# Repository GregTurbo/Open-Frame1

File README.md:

# Pummel Prism Pico (WIP)

An open-source All Button fight stick for traditional fighters, prioritizing small size and 3d printablitiy.

[FeralAI's code (gp2040)](https://github.com/FeralAI/GP2040)

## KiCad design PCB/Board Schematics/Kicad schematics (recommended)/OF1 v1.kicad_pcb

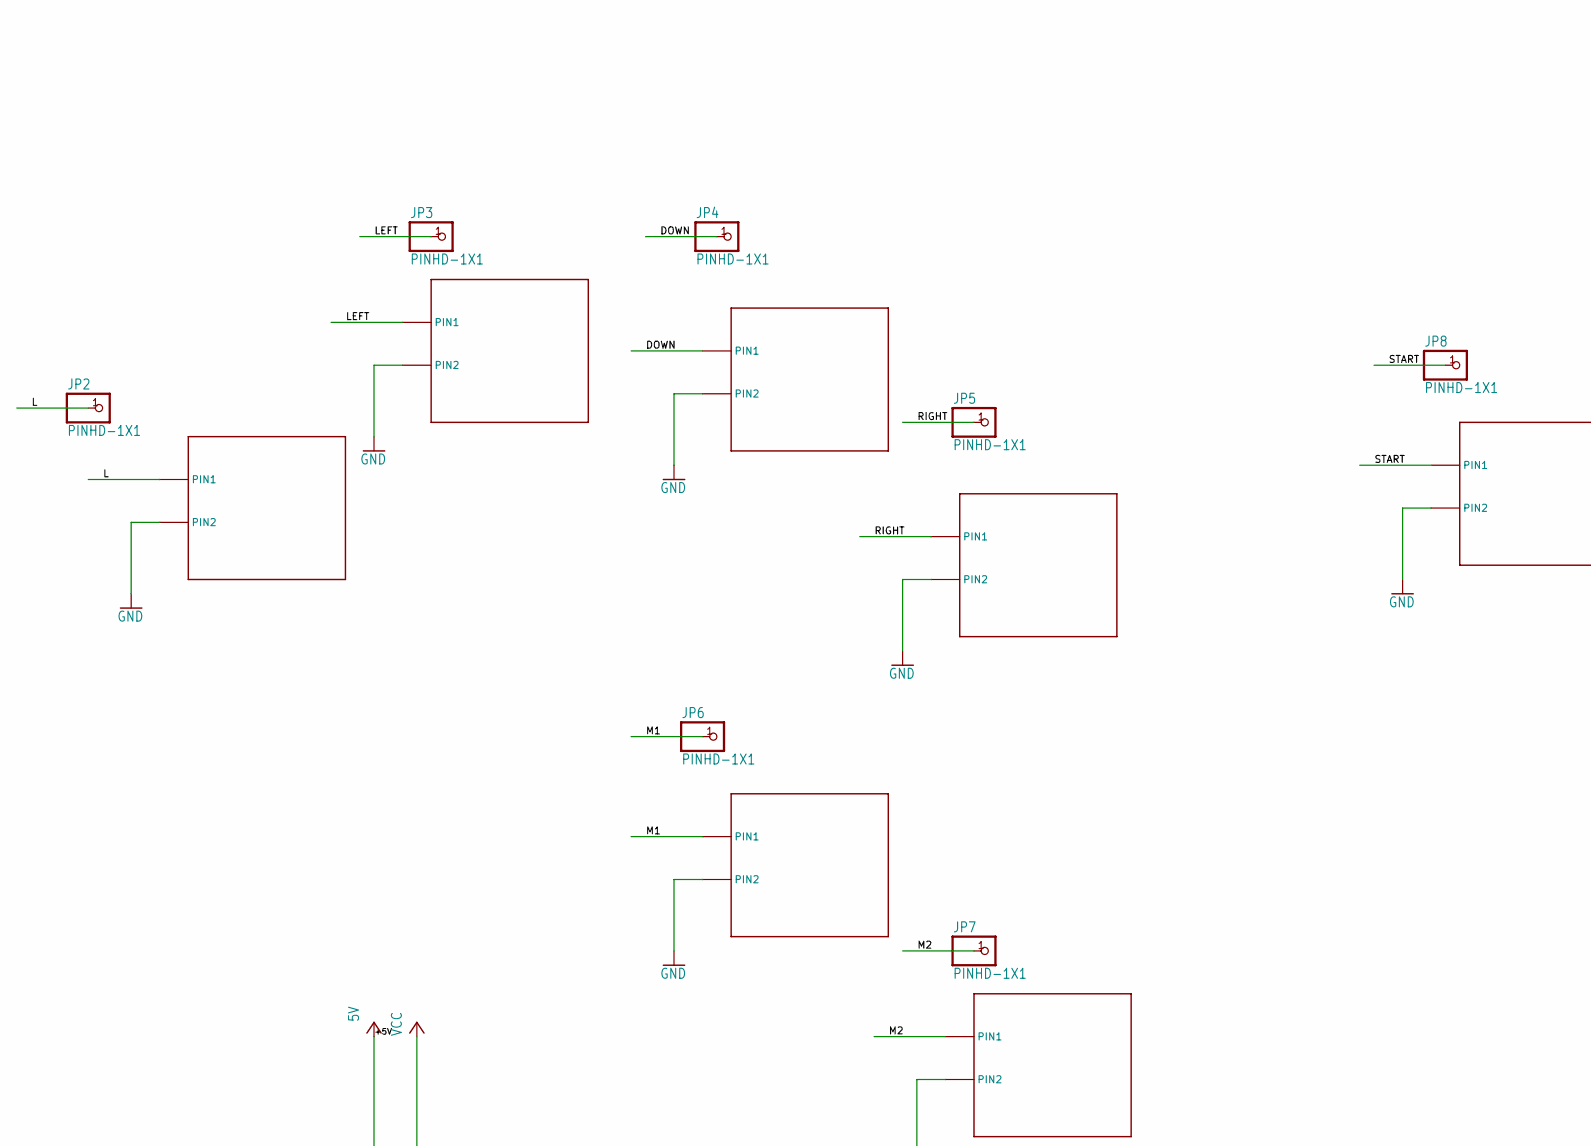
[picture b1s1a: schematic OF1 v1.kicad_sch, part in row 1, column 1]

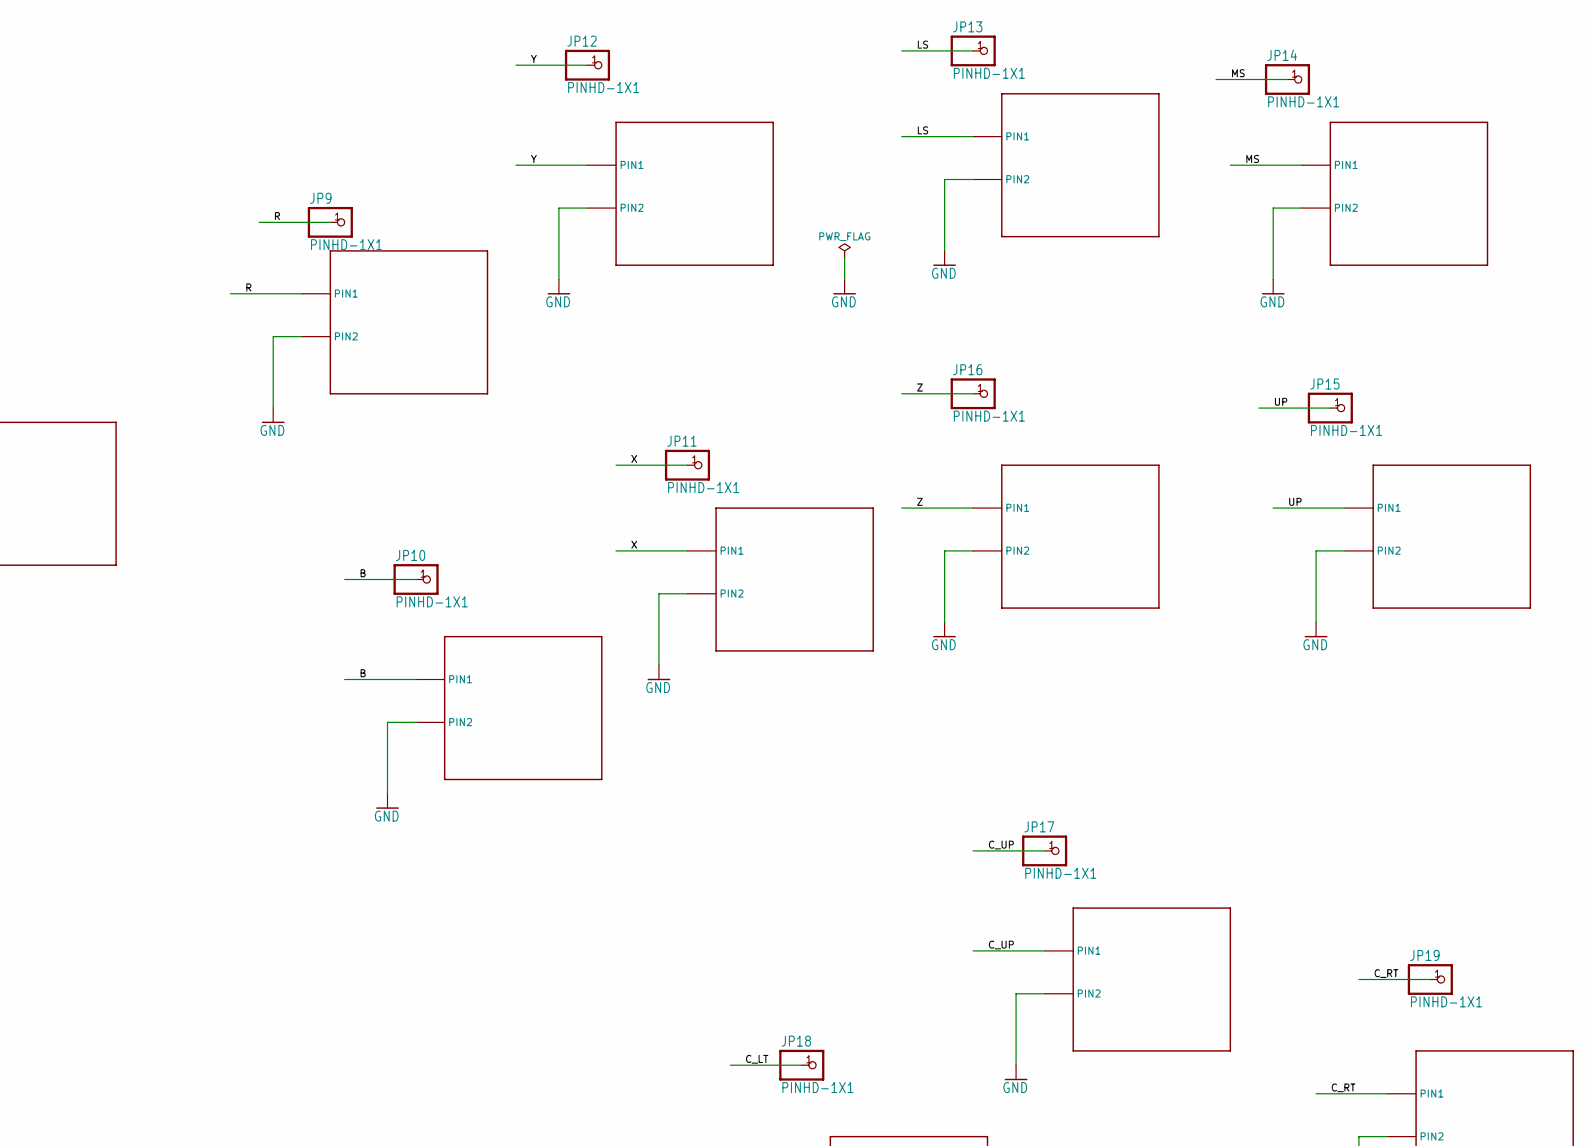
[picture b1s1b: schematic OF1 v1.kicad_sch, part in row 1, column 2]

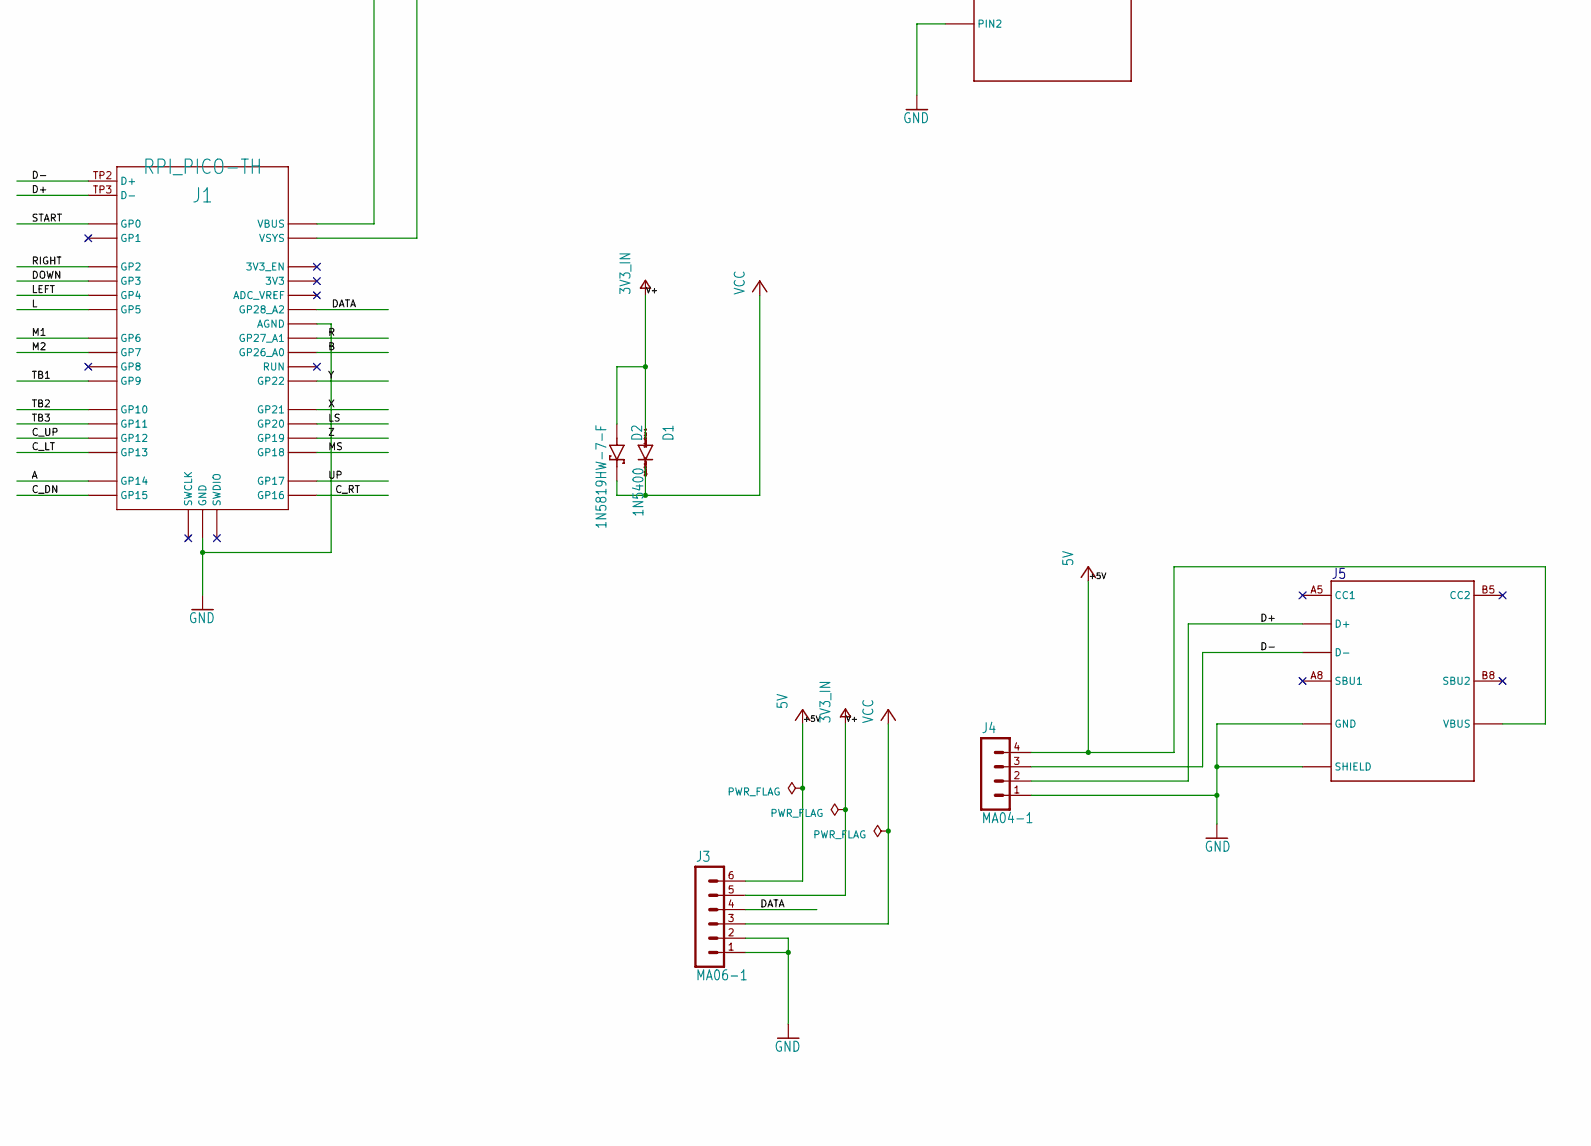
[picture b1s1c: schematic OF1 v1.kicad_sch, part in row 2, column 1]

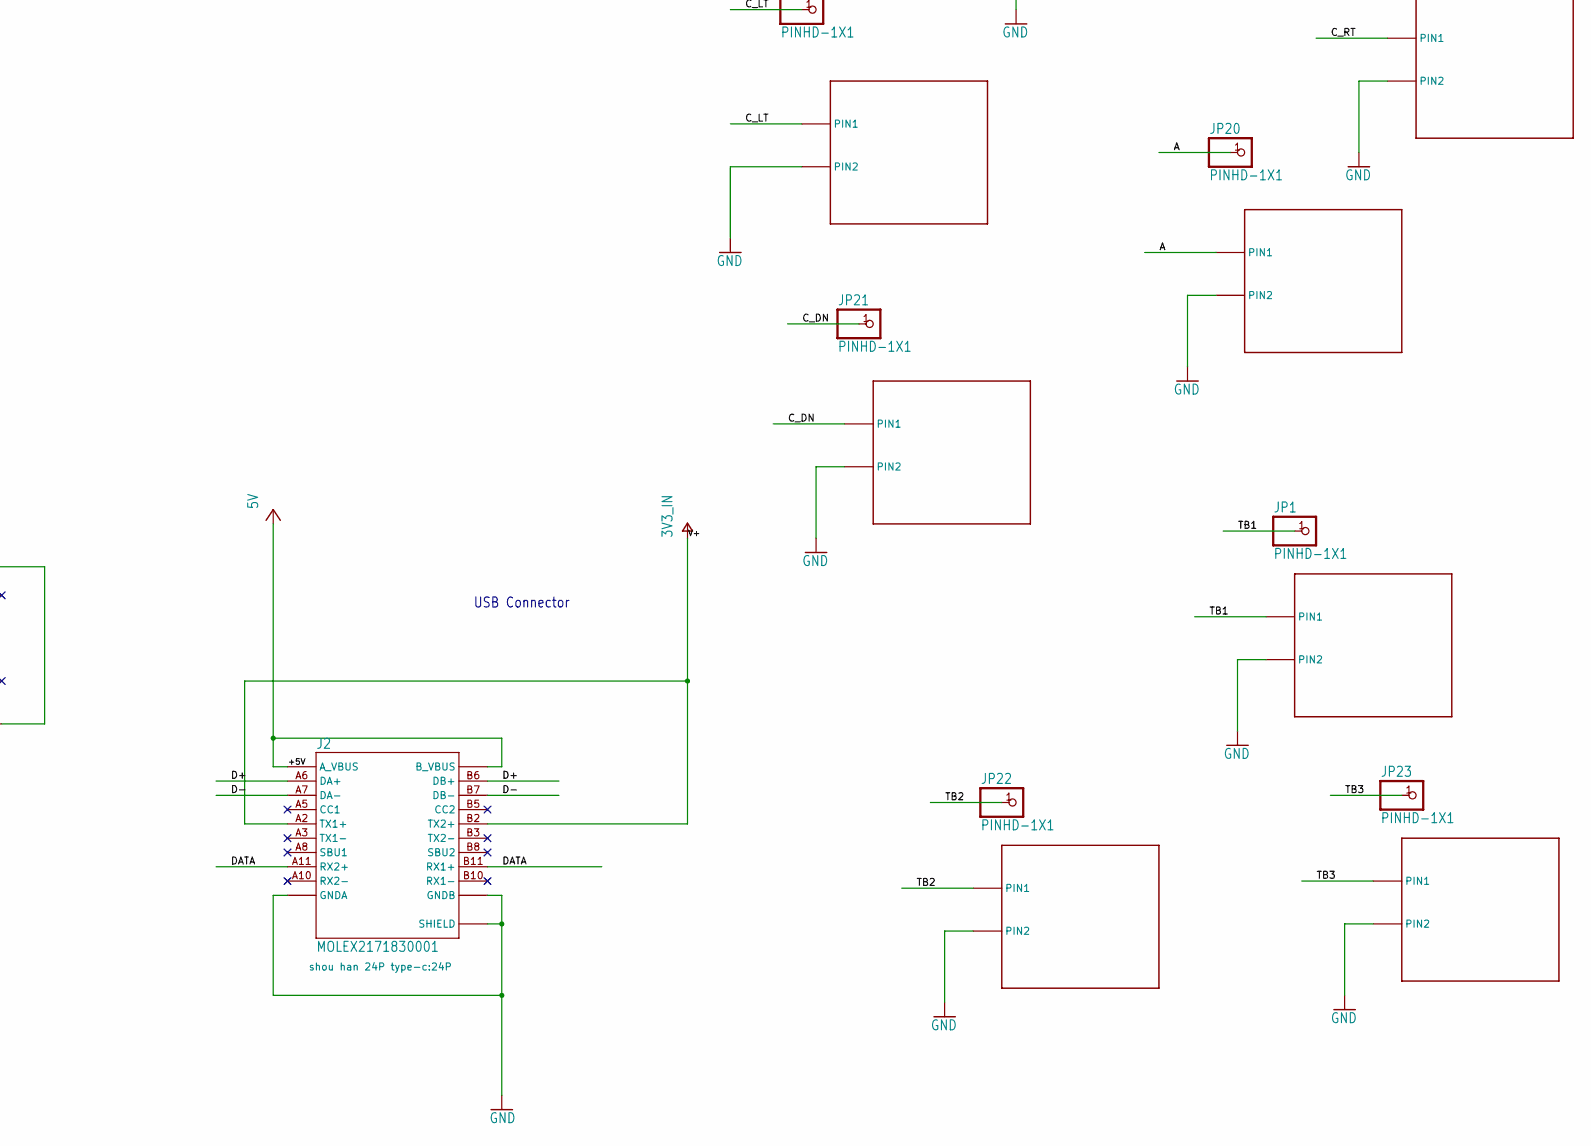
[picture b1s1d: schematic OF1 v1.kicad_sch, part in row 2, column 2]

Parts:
D1: 1N5400; DO201-15
D2: 1N5819HW-7-F; SOD3715X145N
J1: RPI_PICO-TH; RPI_PICO_TH
J2: MOLEX2171830001; 24P
J3: MA06-1
J4: MA04-1
J5: GT-USB-7010; 16P
JP1, JP2, JP3, JP4, JP5, JP6, JP7, JP8, JP9, JP10, JP11, JP12, JP13, JP14, JP15, JP16, JP17, JP18, JP19, JP20, JP21, JP22, JP23: PINHD-1X1; 1X01
U$1, U$2, U$3, U$4, U$5, U$6, U$7, U$8, U$9, U$10, U$11, U$12, U$13, U$14, U$15, U$16, U$17, U$18, U$19, U$20, U$21, U$22, U$23: MX-B; MX-BOTH

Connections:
+5V: J1.VBUS, J2.A4 (A_VBUS), J2.A9 (A_VBUS), J2.B4 (B_VBUS), J2.B9 (B_VBUS), J3.6, J4.4, J5.A4/B9 (VBUS), J5.B4/A9 (VBUS)
/A: J1.GP14, JP20.1, U$20.P$2 (PIN1), U$20.P$3 (PIN1)
/B: J1.GP26_A0, JP10.1, U$13.P$2 (PIN1), U$13.P$3 (PIN1)
/C_DN: J1.GP15, JP21.1, U$21.P$2 (PIN1), U$21.P$3 (PIN1)
/C_LT: J1.GP13, JP18.1, U$18.P$2 (PIN1), U$18.P$3 (PIN1)
/C_RT: J1.GP16, JP19.1, U$19.P$2 (PIN1), U$19.P$3 (PIN1)
/C_UP: J1.GP12, JP17.1, U$17.P$2 (PIN1), U$17.P$3 (PIN1)
/D+: J1.TP3 (D-), J2.A6 (DA+), J2.B6 (DB+), J4.2, J5.A6 (D+), J5.B6 (D+)
/D-: J1.TP2 (D+), J2.A7 (DA-), J2.B7 (DB-), J4.3, J5.A7 (D-), J5.B7 (D-)
/DATA: J1.GP28_A2, J2.A11 (RX2+), J2.B11 (RX1+), J3.4
/DOWN: J1.GP3, JP4.1, U$4.P$2 (PIN1), U$4.P$3 (PIN1)
/L: J1.GP5, JP2.1, U$1.P$2 (PIN1), U$1.P$3 (PIN1)
/LEFT: J1.GP4, JP3.1, U$2.P$2 (PIN1), U$2.P$3 (PIN1)
/LS: J1.GP20, JP13.1, U$11.P$2 (PIN1), U$11.P$3 (PIN1)
/M1: J1.GP6, JP6.1, U$6.P$2 (PIN1), U$6.P$3 (PIN1)
/M2: J1.GP7, JP7.1, U$7.P$2 (PIN1), U$7.P$3 (PIN1)
/MS: J1.GP18, JP14.1, U$12.P$2 (PIN1), U$12.P$3 (PIN1)
/R: J1.GP27_A1, JP9.1, U$9.P$2 (PIN1), U$9.P$3 (PIN1)
/RIGHT: J1.GP2, JP5.1, U$5.P$2 (PIN1), U$5.P$3 (PIN1)
/START: J1.GP0, JP8.1, U$8.P$2 (PIN1), U$8.P$3 (PIN1)
/TB1: J1.GP9, JP1.1, U$3.P$2 (PIN1), U$3.P$3 (PIN1)
/TB2: J1.GP10, JP22.1, U$22.P$2 (PIN1), U$22.P$3 (PIN1)
/TB3: J1.GP11, JP23.1, U$23.P$2 (PIN1), U$23.P$3 (PIN1)
/UP: J1.GP17, JP15.1, U$16.P$2 (PIN1), U$16.P$3 (PIN1)
/X: J1.GP21, JP11.1, U$14.P$2 (PIN1), U$14.P$3 (PIN1)
/Y: J1.GP22, JP12.1, U$10.P$2 (PIN1), U$10.P$3 (PIN1)
/Z: J1.GP19, JP16.1, U$15.P$2 (PIN1), U$15.P$3 (PIN1)
GND: J1.AGND, J1.GND@1 (GND), J1.GND@2 (GND), J1.GND@3 (GND), J1.GND@4 (GND), J1.GND@5 (GND), J1.GND@6 (GND), J1.GND@7 (GND), J1.GND@8 (GND), J2.A1 (GNDA), J2.A12 (GNDA), J2.B1 (GNDB), J2.B12 (GNDB), J2.SHIELD1 (SHIELD), J2.SHIELD2 (SHIELD), J2.SHIELD3 (SHIELD), J2.SHIELD4 (SHIELD), J3.1, J3.2, J4.1, J5.A1/B12 (GND), J5.B1/A12 (GND), J5.SHIELD1 (SHIELD), J5.SHIELD2 (SHIELD), J5.SHIELD3 (SHIELD), J5.SHIELD4 (SHIELD), U$1.P$1 (PIN2), U$1.P$4 (PIN2), U$2.P$1 (PIN2), U$2.P$4 (PIN2), U$3.P$1 (PIN2), U$3.P$4 (PIN2), U$4.P$1 (PIN2), U$4.P$4 (PIN2), U$5.P$1 (PIN2), U$5.P$4 (PIN2), U$6.P$1 (PIN2), U$6.P$4 (PIN2), U$7.P$1 (PIN2), U$7.P$4 (PIN2), U$8.P$1 (PIN2), U$8.P$4 (PIN2), U$9.P$1 (PIN2), U$9.P$4 (PIN2), U$10.P$1 (PIN2), U$10.P$4 (PIN2), U$11.P$1 (PIN2), U$11.P$4 (PIN2), U$12.P$1 (PIN2), U$12.P$4 (PIN2), U$13.P$1 (PIN2), U$13.P$4 (PIN2), U$14.P$1 (PIN2), U$14.P$4 (PIN2), U$15.P$1 (PIN2), U$15.P$4 (PIN2), U$16.P$1 (PIN2), U$16.P$4 (PIN2), U$17.P$1 (PIN2), U$17.P$4 (PIN2), U$18.P$1 (PIN2), U$18.P$4 (PIN2), U$19.P$1 (PIN2), U$19.P$4 (PIN2), U$20.P$1 (PIN2), U$20.P$4 (PIN2), U$21.P$1 (PIN2), U$21.P$4 (PIN2), U$22.P$1 (PIN2), U$22.P$4 (PIN2), U$23.P$1 (PIN2), U$23.P$4 (PIN2)
V+: D1.A, D2.A, J2.A2 (TX1+), J2.B2 (TX2+), J3.5
VCC: D1.C, D2.C (K), J1.VSYS, J3.3

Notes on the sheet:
USB Connector

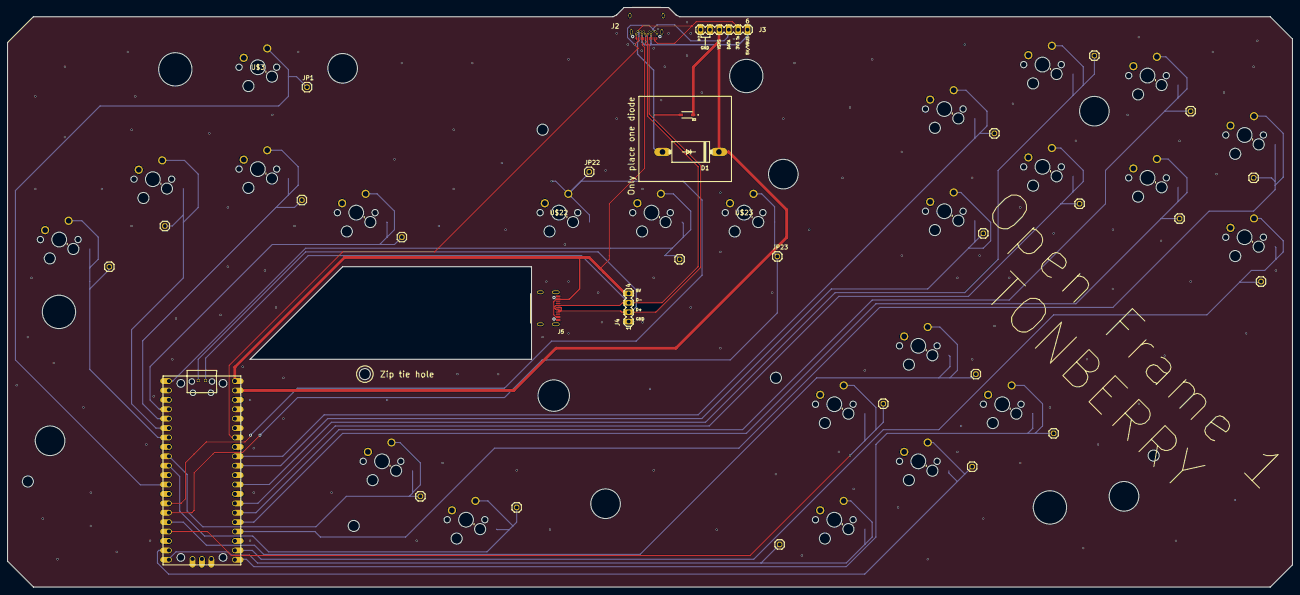
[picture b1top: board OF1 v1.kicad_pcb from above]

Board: 2 copper layers, 347.0 x 156.5 mm, 70 parts (0 on the bottom side), 30 nets.

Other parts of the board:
@HOLE0, @HOLE1, @HOLE2, @HOLE3, @HOLE4, @HOLE5, @HOLE6, @HOLE7, @HOLE8, @HOLE9, @HOLE10, @HOLE11, @HOLE12, @HOLE13, @HOLE14, @HOLE15, @HOLE16: (no value)

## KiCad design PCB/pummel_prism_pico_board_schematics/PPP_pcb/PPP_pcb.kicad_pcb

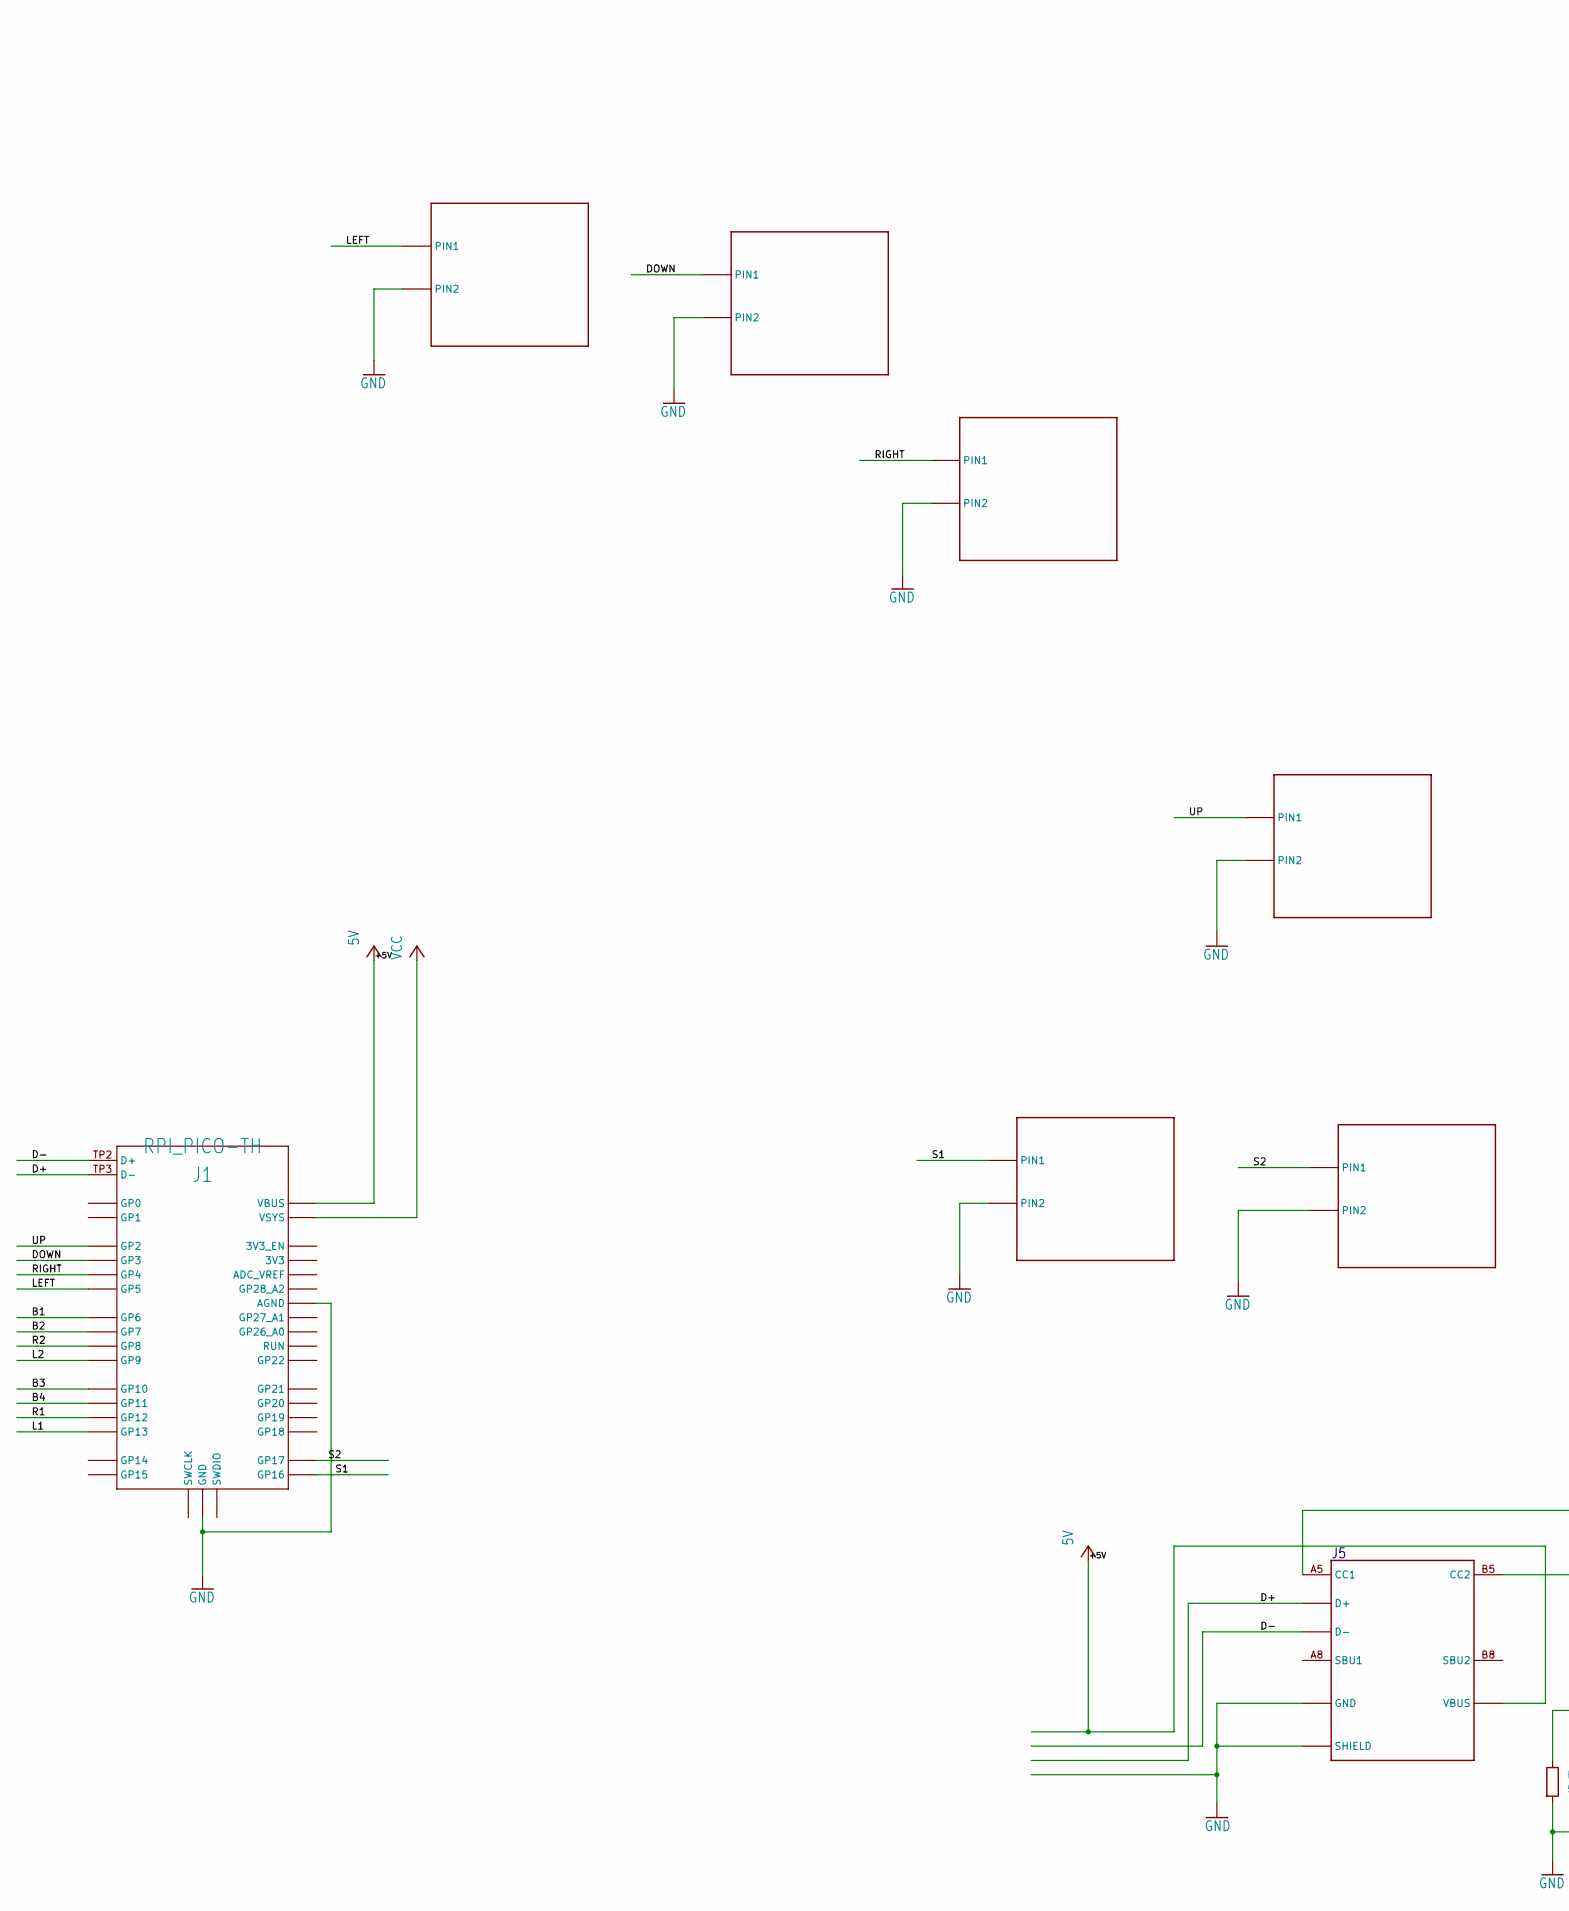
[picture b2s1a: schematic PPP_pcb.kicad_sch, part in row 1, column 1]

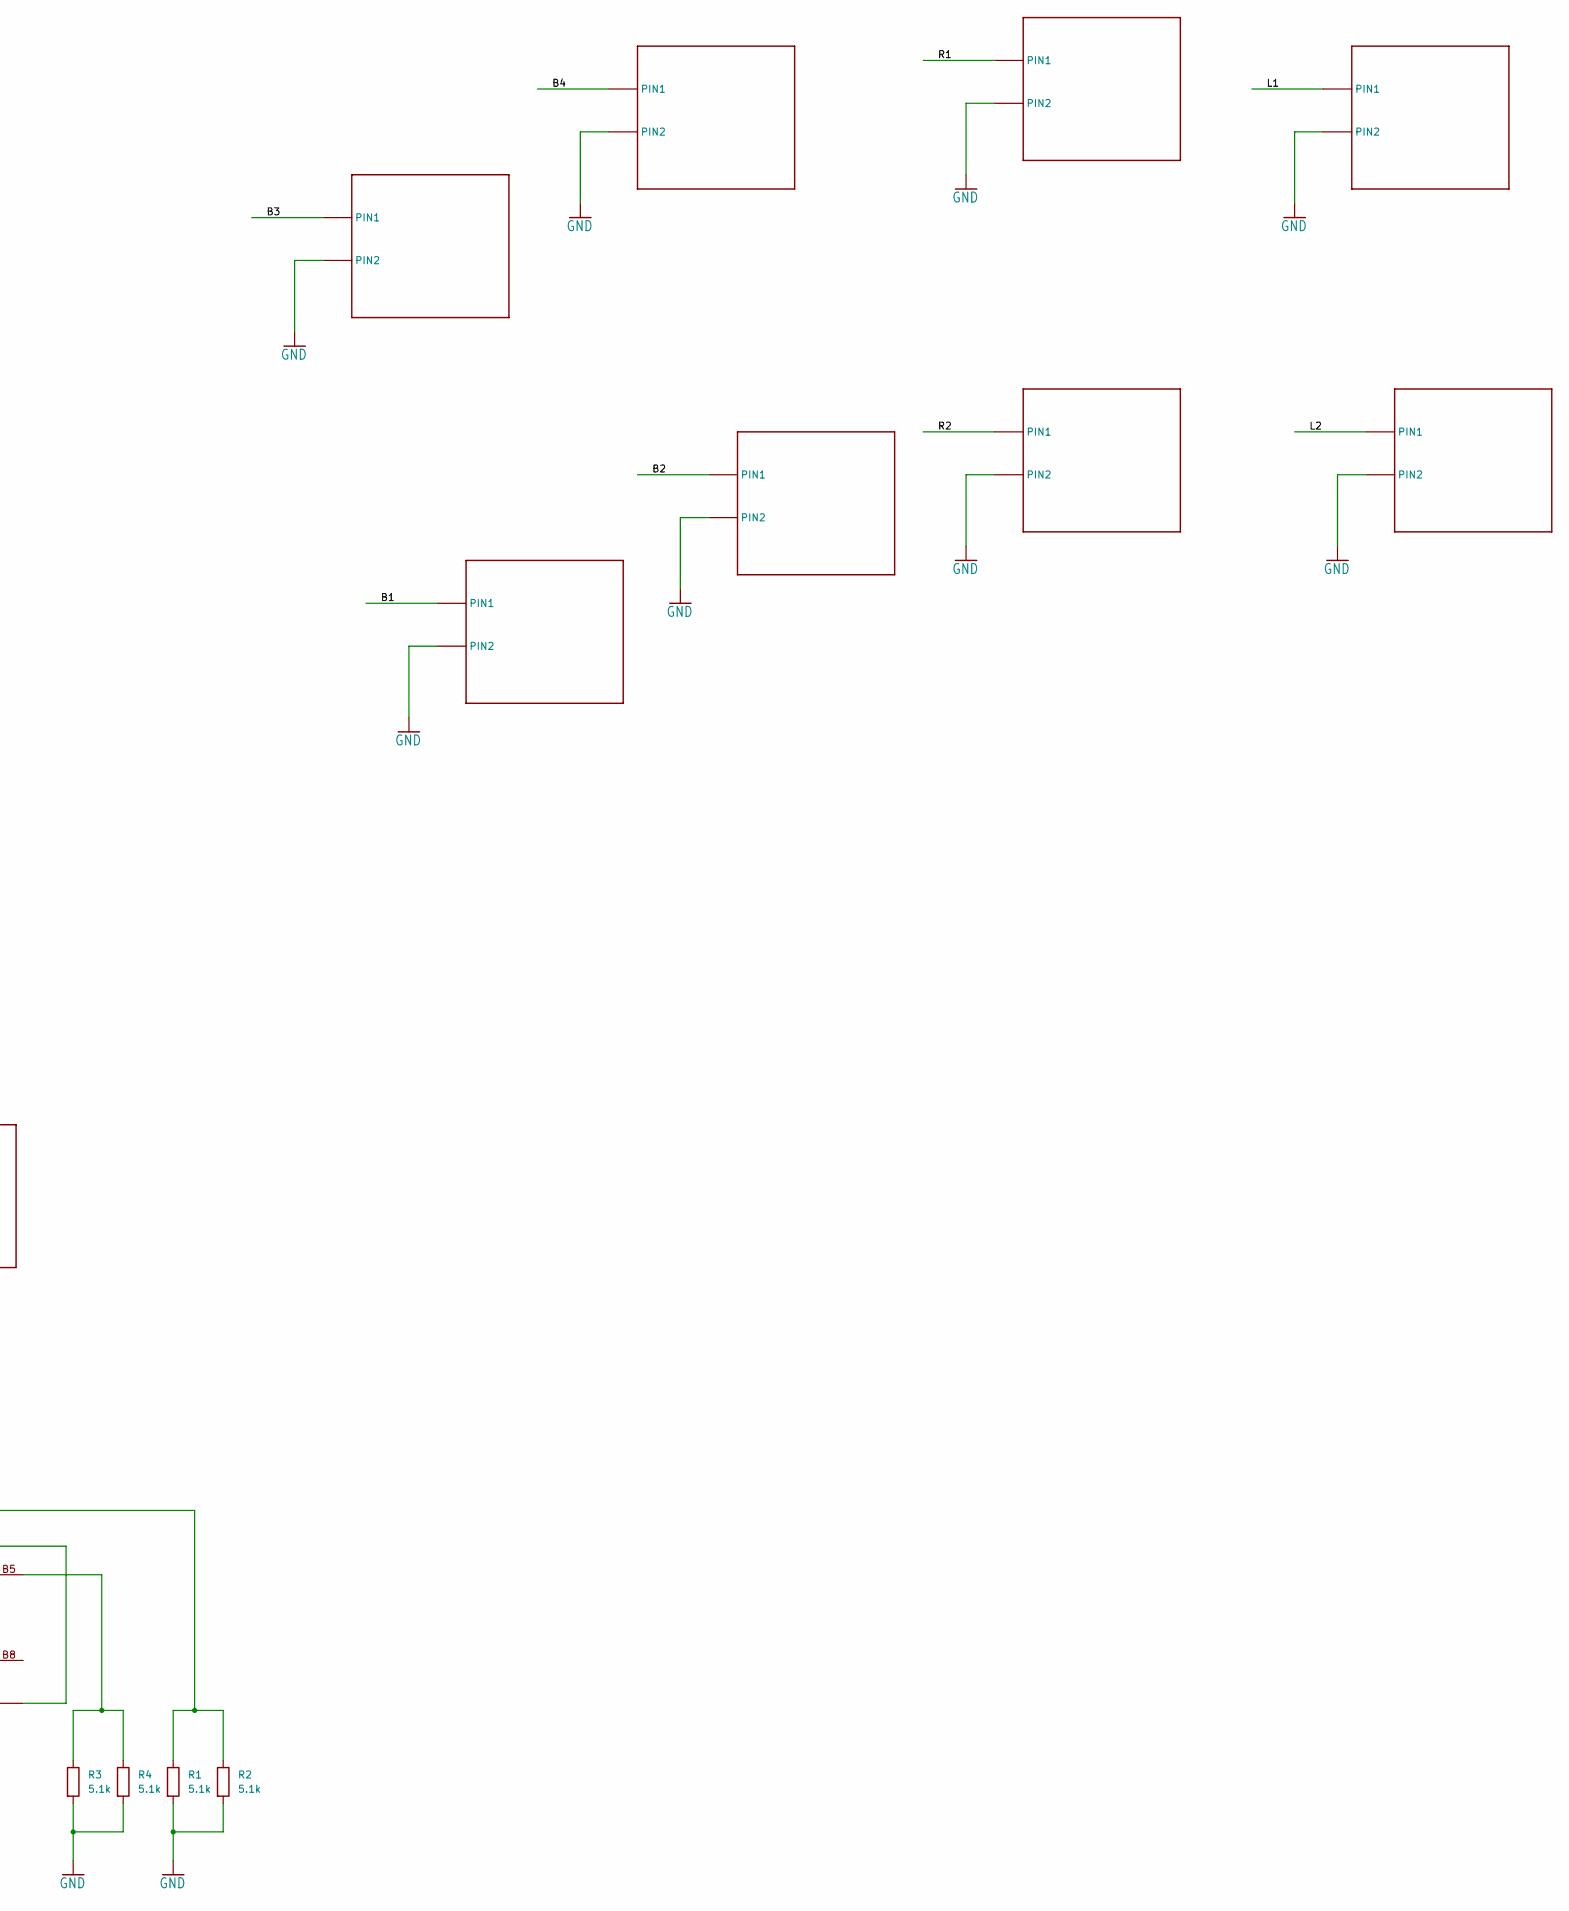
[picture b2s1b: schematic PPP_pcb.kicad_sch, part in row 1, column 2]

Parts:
J1: RPI_PICO-TH; RPI_PICO_TH
J5: GT-USB-7010; 16P
R1, R3: 5.1k; R_Axial_DIN0207_L6.3mm_D2.5mm_P7.62mm_Horizontal
R2, R4: 5.1k; R_0603_1608Metric
U$2, U$4, U$5, U$6, U$8, U$9, U$10, U$11, U$12, U$13, U$14, U$15, U$16, U$18: MX-B; MX-BOTH

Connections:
+5V: J1.VBUS, J5.A4/B9 (VBUS), J5.B4/A9 (VBUS)
/B1: J1.GP6, U$13.P$2 (PIN1), U$13.P$3 (PIN1)
/B2: J1.GP7, U$14.P$2 (PIN1), U$14.P$3 (PIN1)
/B3: J1.GP10, U$9.P$2 (PIN1), U$9.P$3 (PIN1)
/B4: J1.GP11, U$10.P$2 (PIN1), U$10.P$3 (PIN1)
/D+: J1.TP3 (D-), J5.A6 (D+), J5.B6 (D+)
/D-: J1.TP2 (D+), J5.A7 (D-), J5.B7 (D-)
/DOWN: J1.GP3, U$4.P$2 (PIN1), U$4.P$3 (PIN1)
/L1: J1.GP13, U$12.P$2 (PIN1), U$12.P$3 (PIN1)
/L2: J1.GP9, U$16.P$2 (PIN1), U$16.P$3 (PIN1)
/LEFT: J1.GP5, U$2.P$2 (PIN1), U$2.P$3 (PIN1)
/R1: J1.GP12, U$11.P$2 (PIN1), U$11.P$3 (PIN1)
/R2: J1.GP8, U$15.P$2 (PIN1), U$15.P$3 (PIN1)
/RIGHT: J1.GP4, U$5.P$2 (PIN1), U$5.P$3 (PIN1)
/S1: J1.GP16, U$8.P$2 (PIN1), U$8.P$3 (PIN1)
/S2: J1.GP17, U$18.P$2 (PIN1), U$18.P$3 (PIN1)
/UP: J1.GP2, U$6.P$2 (PIN1), U$6.P$3 (PIN1)
GND: J1.AGND, J1.GND@1 (GND), J1.GND@2 (GND), J1.GND@3 (GND), J1.GND@4 (GND), J1.GND@5 (GND), J1.GND@6 (GND), J1.GND@7 (GND), J1.GND@8 (GND), J5.A1/B12 (GND), J5.B1/A12 (GND), J5.SHIELD1 (SHIELD), J5.SHIELD2 (SHIELD), J5.SHIELD3 (SHIELD), J5.SHIELD4 (SHIELD), R1.2, R2.2, R3.2, R4.2, U$2.P$1 (PIN2), U$2.P$4 (PIN2), U$4.P$1 (PIN2), U$4.P$4 (PIN2), U$5.P$1 (PIN2), U$5.P$4 (PIN2), U$6.P$1 (PIN2), U$6.P$4 (PIN2), U$8.P$1 (PIN2), U$8.P$4 (PIN2), U$9.P$1 (PIN2), U$9.P$4 (PIN2), U$10.P$1 (PIN2), U$10.P$4 (PIN2), U$11.P$1 (PIN2), U$11.P$4 (PIN2), U$12.P$1 (PIN2), U$12.P$4 (PIN2), U$13.P$1 (PIN2), U$13.P$4 (PIN2), U$14.P$1 (PIN2), U$14.P$4 (PIN2), U$15.P$1 (PIN2), U$15.P$4 (PIN2), U$16.P$1 (PIN2), U$16.P$4 (PIN2), U$18.P$1 (PIN2), U$18.P$4 (PIN2)
unnamed: J5.A5 (CC1), R1.1, R2.1
unnamed: J5.B5 (CC2), R3.1, R4.1
VCC: J1.VSYS

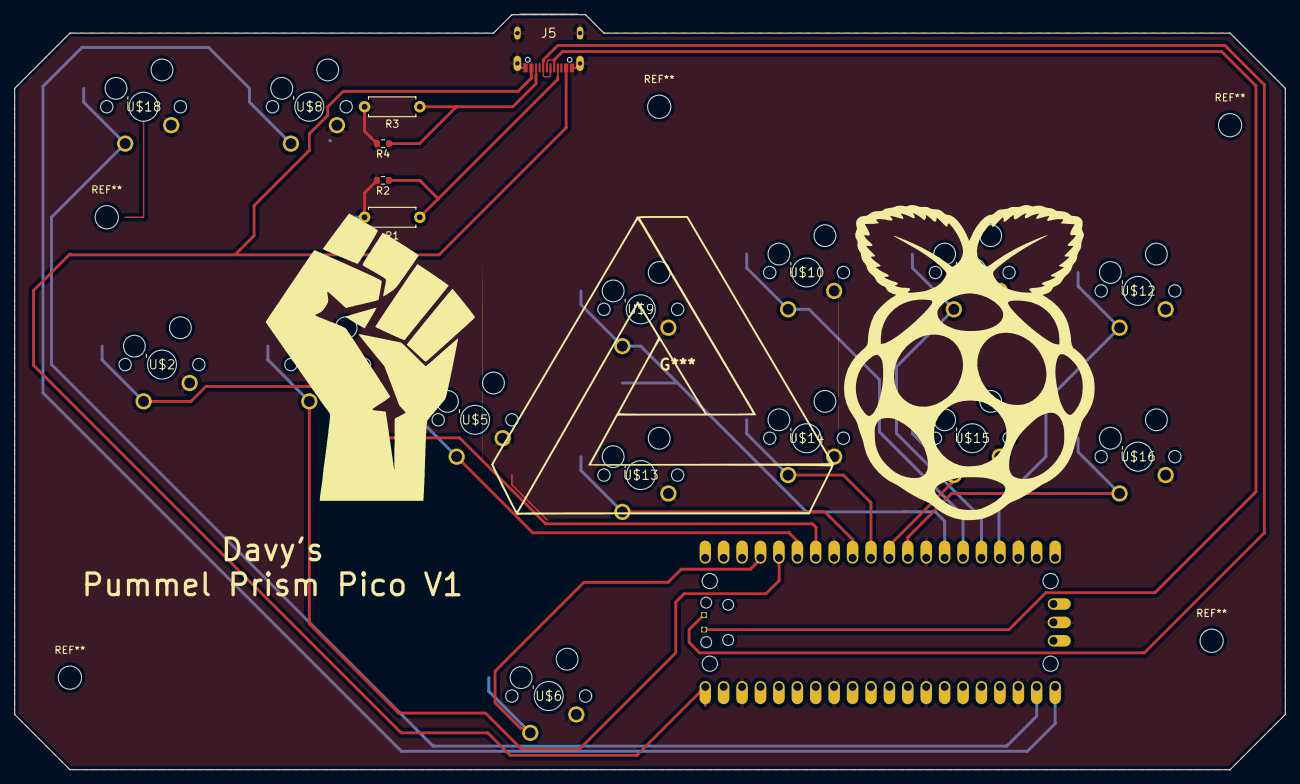
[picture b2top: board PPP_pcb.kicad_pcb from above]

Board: 2 copper layers, 175.3 x 104.1 mm, 20 parts (1 on the bottom side), 20 nets.

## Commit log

2022-06-04 added readme, no images yet
2022-06-15 added images
2022-06-17 Fixed the BOM
2022-08-11 Added Kicad version
    Moved to Kicad to avoid slotted hole issues with JLC
2022-10-10 Wip COMMIT
2022-10-11 adding usbc support to the pcb. Updating fab files to reflect
2023-02-01 checked to make sure all files are good
2023-02-14 feat: tonberry mod
2023-04-12 added ordering guide
2023-04-12 adding updated fab files
2023-04-13 added case Read Me
2024-02-11 1.04, new hotswap socket footprint
